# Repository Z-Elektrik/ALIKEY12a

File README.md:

## ALIKEY12a - Tlacidlova doska 4x3

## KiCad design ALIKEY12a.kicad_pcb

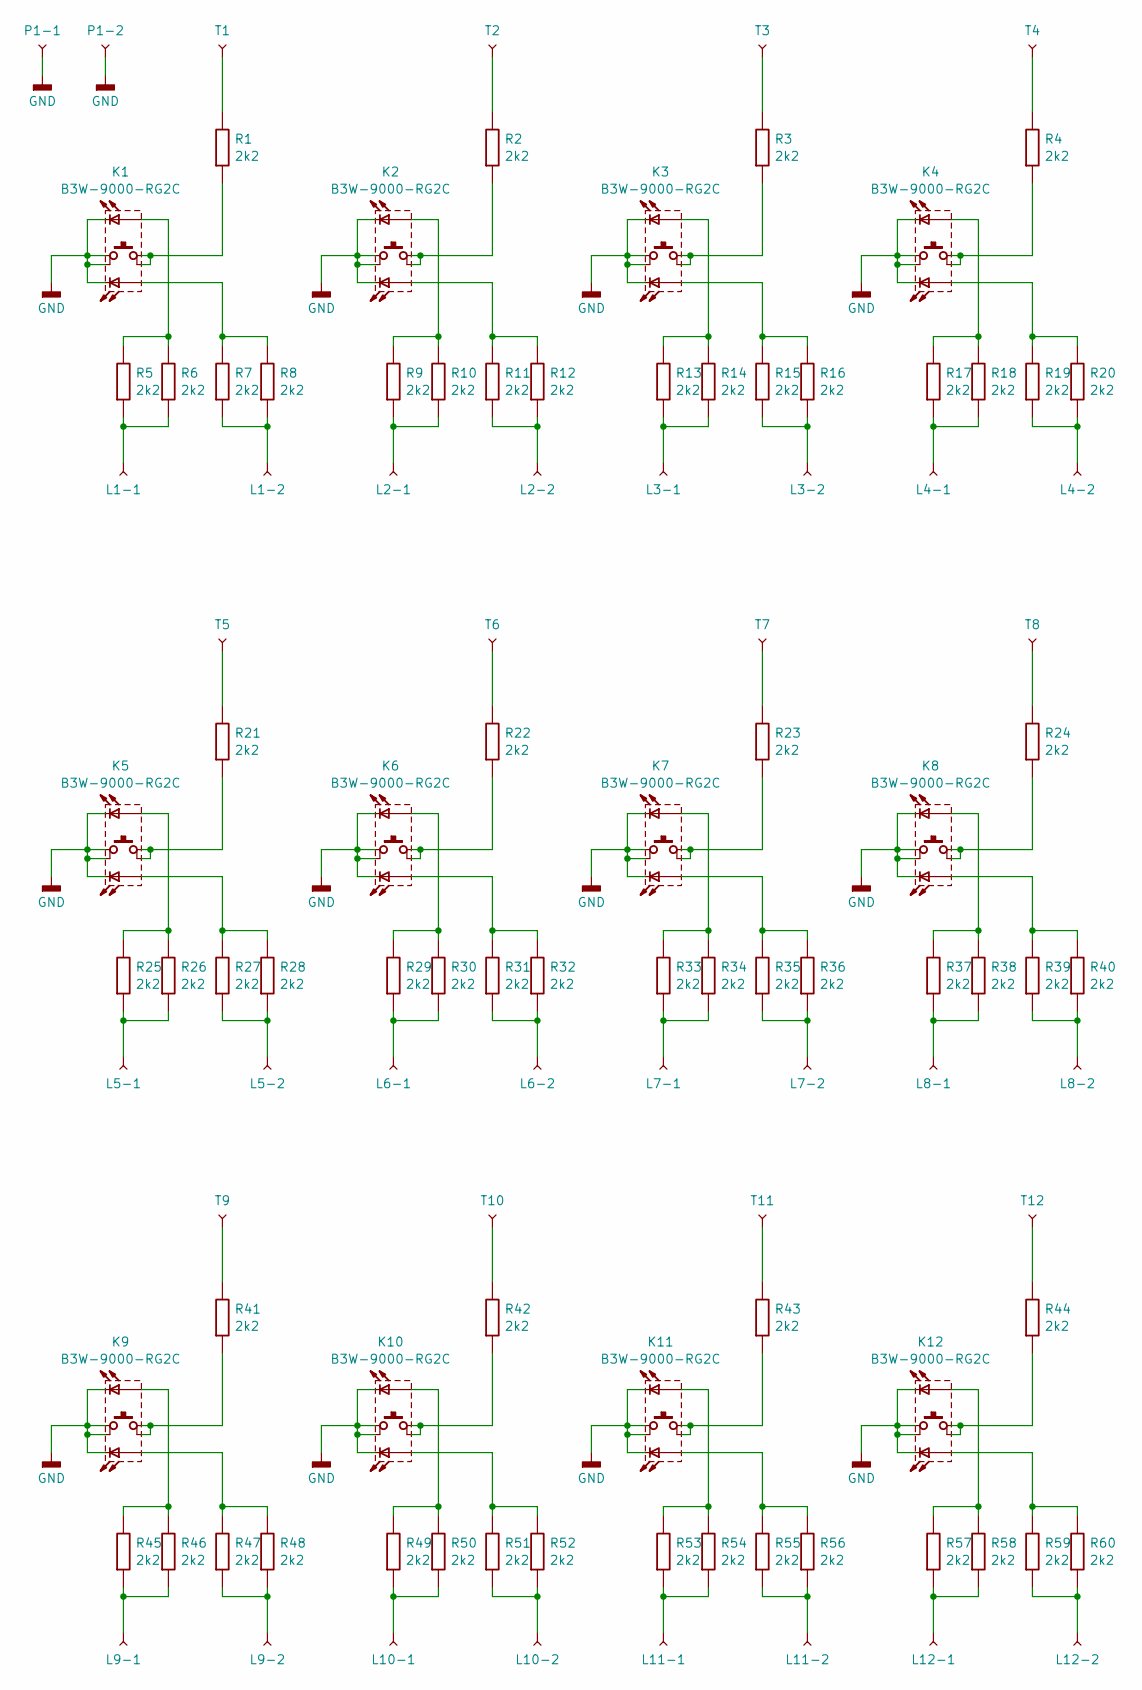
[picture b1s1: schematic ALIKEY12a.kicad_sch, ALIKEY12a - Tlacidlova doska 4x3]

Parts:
K1, K2, K3, K4, K5, K6, K7, K8, K9, K10, K11, K12: B3W-9000-RG2C; B3W-900x-x2xN_Omron; MPN B3W-9000-RG2C
L1-1, L1-2, L2-1, L2-2, L3-1, L3-2, L4-1, L4-2, L5-1, L5-2, L6-1, L6-2, L7-1, L7-2, L8-1, L8-2, L9-1, L9-2, L10-1, L10-2, L11-1, L11-2, L12-1, L12-2: TestPoint; SMD_PAD_R200_445R50
P1-1, P1-2: TestPoint; SMD_PAD_R200_445R50
R1, R2, R3, R4, R5, R6, R7, R8, R9, R10, R11, R12, R13, R14, R15, R16, R17, R18, R19, R20, R21, R22, R23, R24, R25, R26, R27, R28, R29, R30, R31, R32, R33, R34, R35, R36, R37, R38, R39, R40, R41, R42, R43, R44, R45, R46, R47, R48, R49, R50, R51, R52, R53, R54, R55, R56, R57, R58, R59, R60: 2k2; RESC3116X65N_1206
T1, T2, T3, T4, T5, T6, T7, T8, T9, T10, T11, T12: TestPoint; SMD_PAD_R200_445R50

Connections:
GND_Bar: K1.1, K1.2, K1.C1, K1.C2, K2.1, K2.2, K2.C1, K2.C2, K3.1, K3.2, K3.C1, K3.C2, K4.1, K4.2, K4.C1, K4.C2, K5.1, K5.2, K5.C1, K5.C2, K6.1, K6.2, K6.C1, K6.C2, K7.1, K7.2, K7.C1, K7.C2, K8.1, K8.2, K8.C1, K8.C2, K9.1, K9.2, K9.C1, K9.C2, K10.1, K10.2, K10.C1, K10.C2, K11.1, K11.2, K11.C1, K11.C2, K12.1, K12.2, K12.C1, K12.C2, P1-1.1, P1-2.1
unnamed: K1.3, K1.4, R1.1
unnamed: K1.A1, R7.2, R8.2
unnamed: K1.A2, R5.2, R6.2
unnamed: K2.3, K2.4, R2.1
unnamed: K2.A1, R11.2, R12.2
unnamed: K2.A2, R9.2, R10.2
unnamed: K3.3, K3.4, R3.1
unnamed: K3.A1, R15.2, R16.2
unnamed: K3.A2, R13.2, R14.2
unnamed: K4.3, K4.4, R4.1
unnamed: K4.A1, R19.2, R20.2
unnamed: K4.A2, R17.2, R18.2
unnamed: K5.3, K5.4, R21.1
unnamed: K5.A1, R27.2, R28.2
unnamed: K5.A2, R25.2, R26.2
unnamed: K6.3, K6.4, R22.1
unnamed: K6.A1, R31.2, R32.2
unnamed: K6.A2, R29.2, R30.2
unnamed: K7.3, K7.4, R23.1
unnamed: K7.A1, R35.2, R36.2
unnamed: K7.A2, R33.2, R34.2
unnamed: K8.3, K8.4, R24.1
unnamed: K8.A1, R39.2, R40.2
unnamed: K8.A2, R37.2, R38.2
unnamed: K9.3, K9.4, R41.1
unnamed: K9.A1, R47.2, R48.2
unnamed: K9.A2, R45.2, R46.2
unnamed: K10.3, K10.4, R42.1
unnamed: K10.A1, R51.2, R52.2
unnamed: K10.A2, R49.2, R50.2
unnamed: K11.3, K11.4, R43.1
unnamed: K11.A1, R55.2, R56.2
unnamed: K11.A2, R53.2, R54.2
unnamed: K12.3, K12.4, R44.1
unnamed: K12.A1, R59.2, R60.2
unnamed: K12.A2, R57.2, R58.2
unnamed: L1-1.1, R5.1, R6.1
unnamed: L1-2.1, R7.1, R8.1
unnamed: L2-1.1, R9.1, R10.1
unnamed: L2-2.1, R11.1, R12.1
unnamed: L3-1.1, R13.1, R14.1
unnamed: L3-2.1, R15.1, R16.1
unnamed: L4-1.1, R17.1, R18.1
unnamed: L4-2.1, R19.1, R20.1
unnamed: L5-1.1, R25.1, R26.1
unnamed: L5-2.1, R27.1, R28.1
unnamed: L6-1.1, R29.1, R30.1
unnamed: L6-2.1, R31.1, R32.1
unnamed: L7-1.1, R33.1, R34.1
unnamed: L7-2.1, R35.1, R36.1
unnamed: L8-1.1, R37.1, R38.1
unnamed: L8-2.1, R39.1, R40.1
unnamed: L9-1.1, R45.1, R46.1
unnamed: L9-2.1, R47.1, R48.1
unnamed: L10-1.1, R49.1, R50.1
unnamed: L10-2.1, R51.1, R52.1
unnamed: L11-1.1, R53.1, R54.1
unnamed: L11-2.1, R55.1, R56.1
unnamed: L12-1.1, R57.1, R58.1
unnamed: L12-2.1, R59.1, R60.1
unnamed: R1.2, T1.1
unnamed: R2.2, T2.1
unnamed: R3.2, T3.1
unnamed: R4.2, T4.1
unnamed: R21.2, T5.1
unnamed: R22.2, T6.1
unnamed: R23.2, T7.1
unnamed: R24.2, T8.1
unnamed: R41.2, T9.1
unnamed: R42.2, T10.1
unnamed: R43.2, T11.1
unnamed: R44.2, T12.1

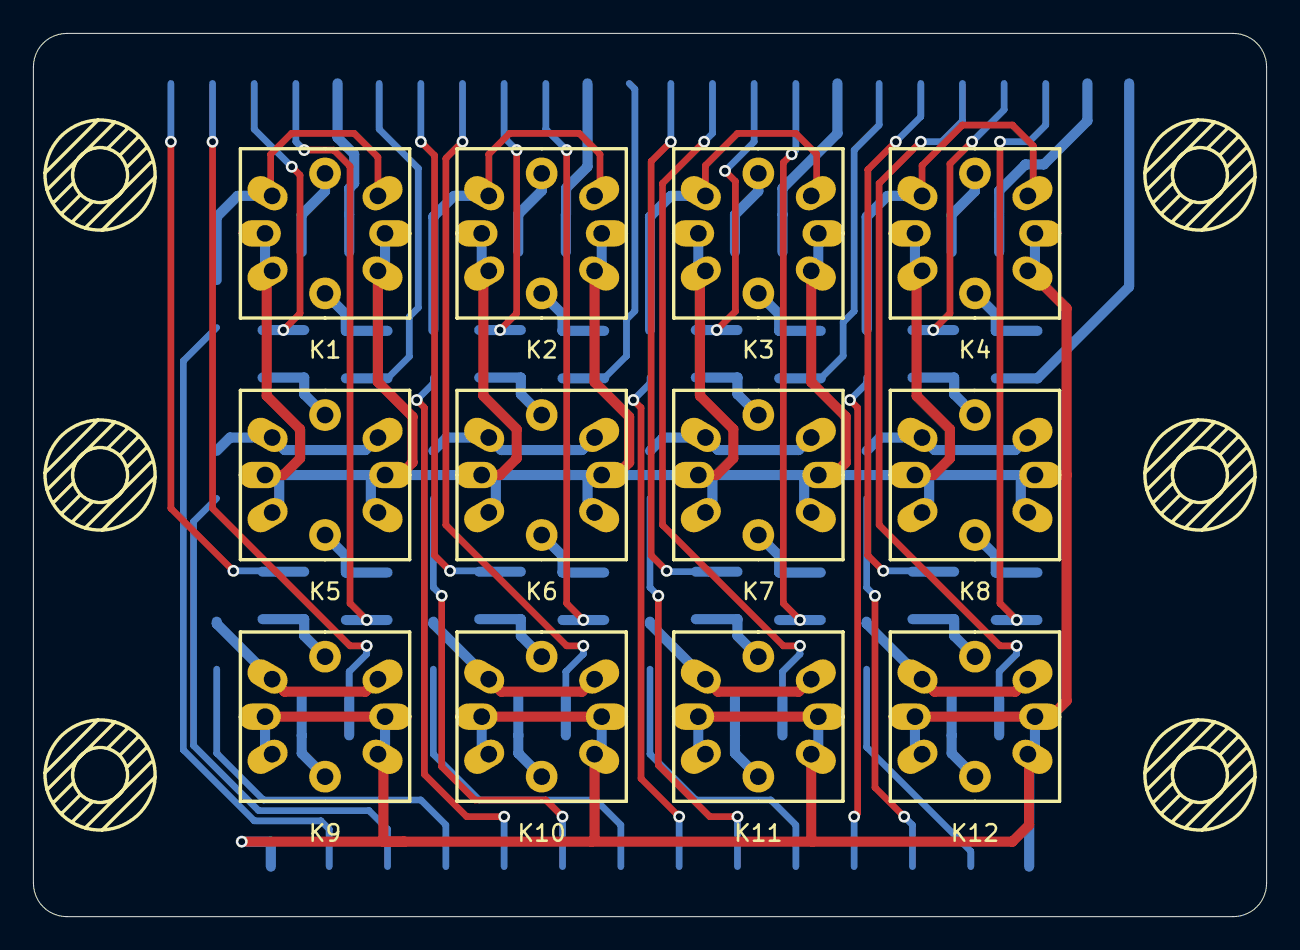
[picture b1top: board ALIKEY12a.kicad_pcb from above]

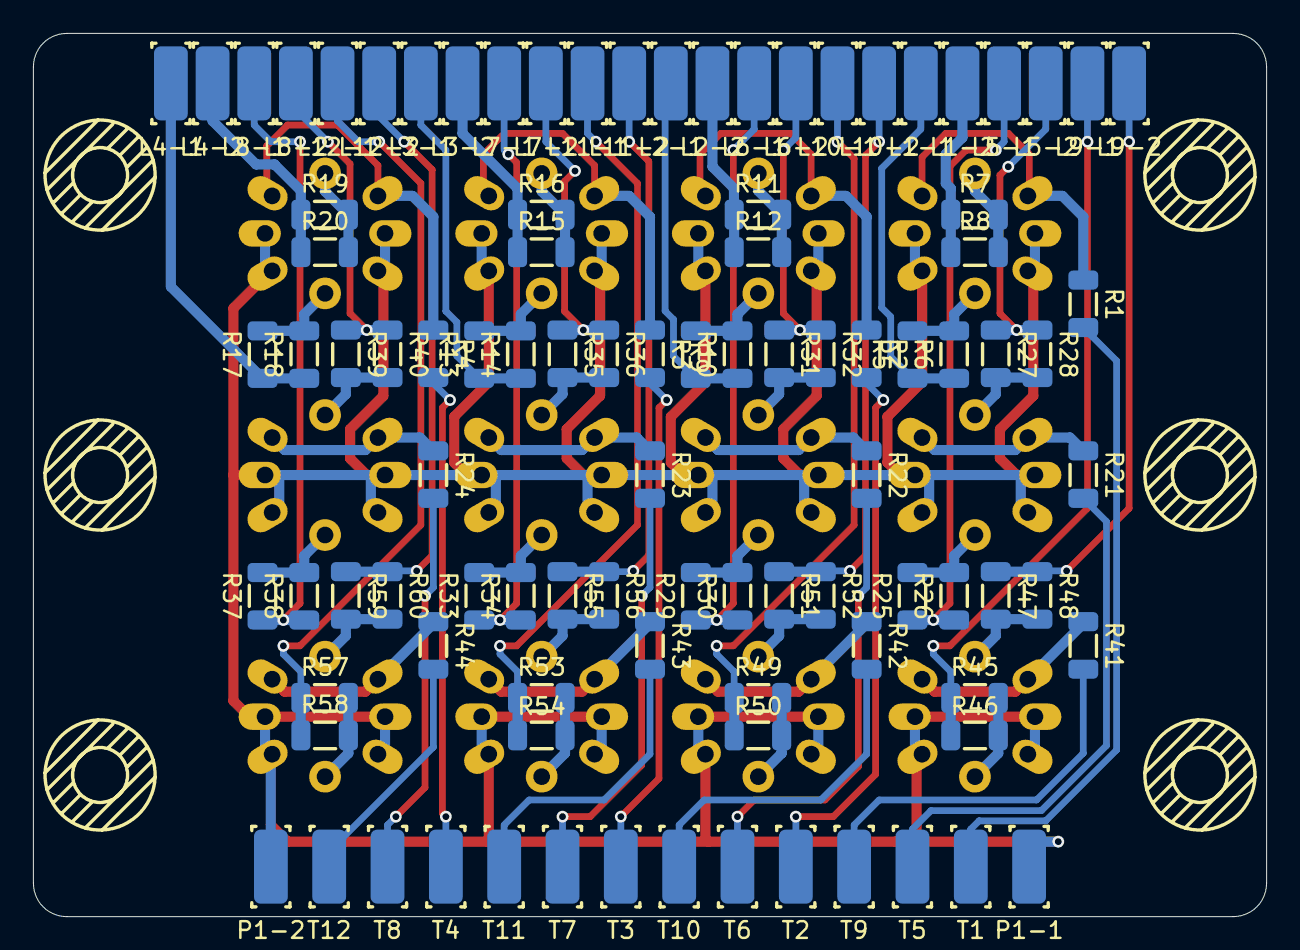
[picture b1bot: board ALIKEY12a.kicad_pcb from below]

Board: 2 copper layers, 74.0 x 53.0 mm, 110 parts (98 on the bottom side), 73 nets.

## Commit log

2024-10-24 Add step model
2024-10-24 add preview
